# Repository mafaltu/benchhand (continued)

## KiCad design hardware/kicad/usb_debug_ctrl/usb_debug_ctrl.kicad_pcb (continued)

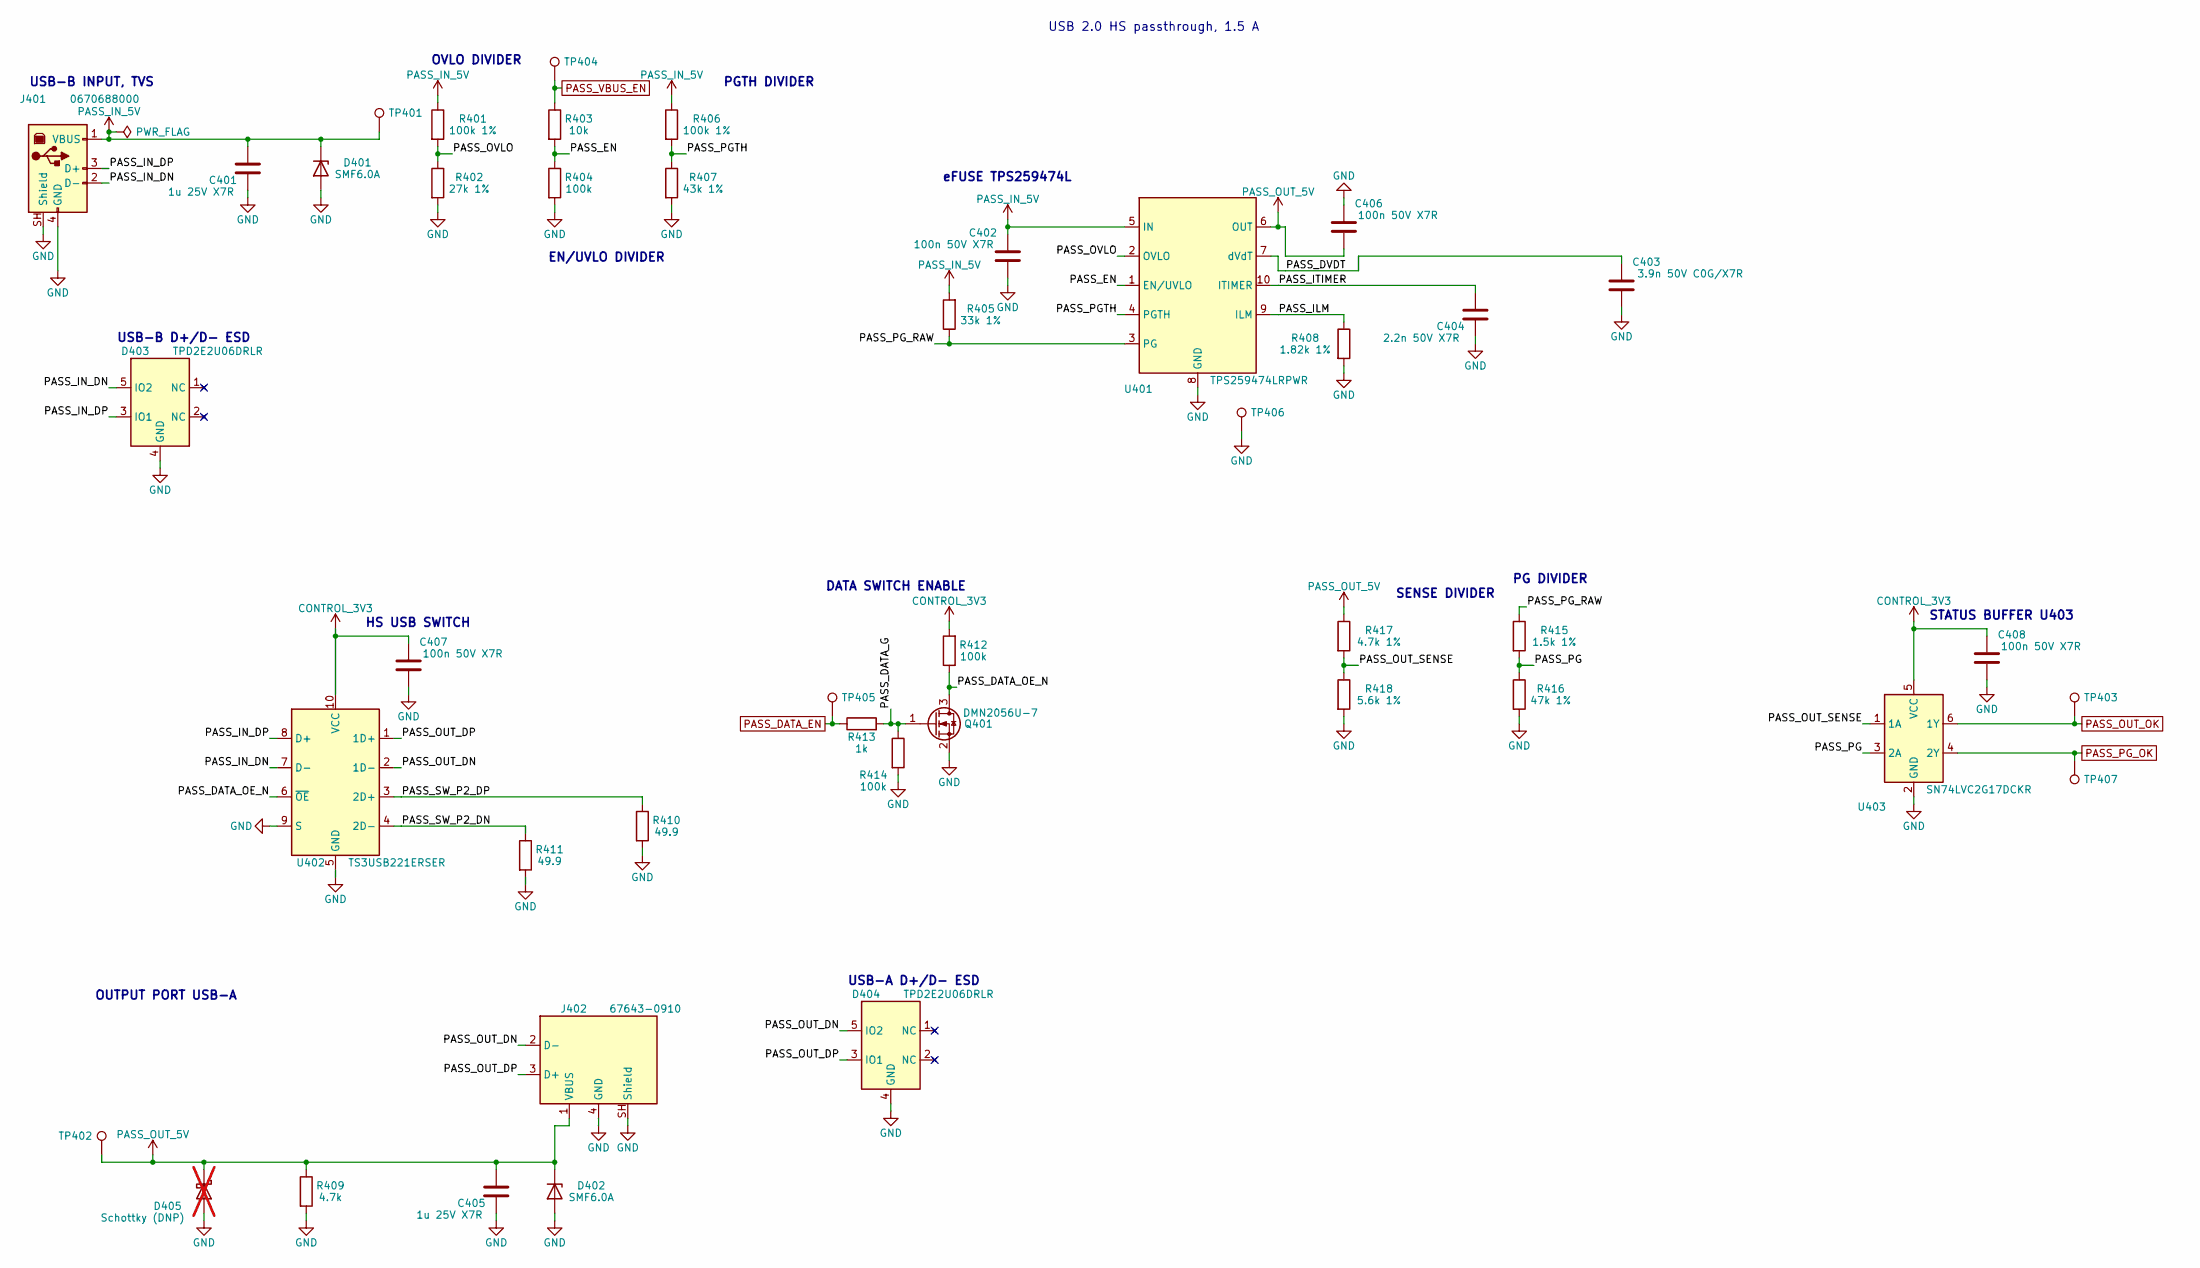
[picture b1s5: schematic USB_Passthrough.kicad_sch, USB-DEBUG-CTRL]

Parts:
C401, C405: 1u 25V X7R; C_0805_2012Metric; MPN CL21B105KAFNNNE
C402, C406, C407, C408: 100n 50V X7R; C_0603_1608Metric; MPN CC0603KRX7R9BB104
C403: 3.9n 50V C0G/X7R; C_0603_1608Metric; MPN CC0603KRX7R9BB392
C404: 2.2n 50V X7R; C_0603_1608Metric; MPN CL10B222KB8NNNC
D401, D402: SMF6.0A; D_SOD-123F_usb_relay; MPN SMF6.0A
D403, D404: TPD2E2U06DRLR; Texas_R-PDSO-N5_DRL-5_usb_relay; MPN TPD2E2U06DRLR
D405: Schottky (DNP); D_SOD-123; MPN none (DNP, MPN chosen only if the bench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; not fitted
J401: 0670688000; USB_B_Molex_67068-8000_Horizontal; MPN 0670688000
J402: 67643-0910; USB_A_Molex_67643_Horizontal; MPN 67643-0910
Q401: DMN2056U-7; SOT-23; MPN DMN2056U-7
R401, R406: 100k 1%; R_0603_1608Metric; MPN RC0603FR-07100KL
R402: 27k 1%; R_0603_1608Metric; MPN RC0603FR-0727KL
R403: 10k; R_0603_1608Metric; MPN RC0603FR-0710KL
R404, R412, R414: 100k; R_0603_1608Metric; MPN RC0603FR-07100KL
R405: 33k 1%; R_0603_1608Metric; MPN RC0603FR-0733KL
R407: 43k 1%; R_0603_1608Metric; MPN RC0603FR-0743KL
R408: 1.82k 1%; R_0603_1608Metric; MPN RC0603FR-071K82L
R409: 4.7k; R_0603_1608Metric; MPN RC0603FR-074K7L
R410, R411: 49.9; R_0603_1608Metric; MPN RC0603FR-0749R9L
R413: 1k; R_0603_1608Metric; MPN RC0603FR-071KL
R415: 1.5k 1%; R_0603_1608Metric; MPN RC0603FR-071K5L
R416: 47k 1%; R_0603_1608Metric; MPN RC0603FR-0747KL
R417: 4.7k 1%; R_0603_1608Metric; MPN RC0603FR-074K7L
R418: 5.6k 1%; R_0603_1608Metric; MPN RC0603FR-075K6L
TP401, TP402, TP403, TP404, TP405, TP406, TP407: test pad 1.0 mm; TestPoint_Pad_D1.0mm; MPN none (copper only)
U401: TPS259474LRPWR; Texas_RPW0010A_VQFN-HR-10_2x2mm; MPN TPS259474LRPWR
U402: TS3USB221ERSER; Texas_UQFN-10_1.5x2mm_P0.5mm_usb_relay; MPN TS3USB221ERSER
U403: SN74LVC2G17DCKR; SOT-363_SC-70-6; MPN SN74LVC2G17DCKR

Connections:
/USB_Passthrough/PASS_DATA_G: Q401.1 (G), R413.2, R414.1
/USB_Passthrough/PASS_DATA_OE_N: Q401.3 (D), R412.1, U402.6 (~OE)
/USB_Passthrough/PASS_DVDT: C403.1, U401.7 (dVdT)
/USB_Passthrough/PASS_EN: R403.2, R404.1, U401.1 (EN/UVLO)
/USB_Passthrough/PASS_ILM: R408.1, U401.9 (ILM)
/USB_Passthrough/PASS_IN_DN: D403.5 (IO2), J401.2 (D-), U402.7 (D-)
/USB_Passthrough/PASS_IN_DP: D403.3 (IO1), J401.3 (D+), U402.8 (D+)
/USB_Passthrough/PASS_ITIMER: C404.1, U401.10 (ITIMER)
/USB_Passthrough/PASS_OUT_DN: D404.5 (IO2), J402.2 (D-), U402.2 (1D-)
/USB_Passthrough/PASS_OUT_DP: D404.3 (IO1), J402.3 (D+), U402.1 (1D+)
/USB_Passthrough/PASS_OUT_SENSE: R417.2, R418.1, U403.1 (1A)
/USB_Passthrough/PASS_OVLO: R401.2, R402.1, U401.2 (OVLO)
/USB_Passthrough/PASS_PG: R415.2, R416.1, U403.3 (2A)
/USB_Passthrough/PASS_PGTH: R406.2, R407.1, U401.4 (PGTH)
/USB_Passthrough/PASS_PG_RAW: R405.1, R415.1, U401.3 (PG)
/USB_Passthrough/PASS_SW_P2_DN: R411.1, U402.4 (2D-)
/USB_Passthrough/PASS_SW_P2_DP: R410.1, U402.3 (2D+)
CONTROL_3V3: C407.1, C408.1, R412.2, U402.10 (VCC), U403.5 (VCC); also elsewhere on the board
GND: C401.2, C402.2, C403.2, C404.2, C405.2, C406.2, C407.2, C408.2, D401.2 (A), D402.2 (A), D403.4 (GND), D404.4 (GND), D405.2 (A), J401.4 (GND), J401.SH (Shield), J402.4 (GND), J402.SH (Shield), Q401.2 (S), R402.2, R404.2, R407.2, R408.2, R409.2, R410.2, R411.2, R414.2, R416.2, R418.2, TP406.1, U401.8 (GND), U402.5 (GND), U402.9 (S), U403.2 (GND); also elsewhere on the board
PASS_DATA_EN: R413.1, TP405.1; also elsewhere on the board
PASS_IN_5V: C401.1, C402.1, D401.1 (K), J401.1 (VBUS), R401.1, R405.2, R406.1, TP401.1, U401.5 (IN)
PASS_OUT_5V: C405.1, C406.1, D402.1 (K), D405.1 (K), J402.1 (VBUS), R409.1, R417.1, TP402.1, U401.6 (OUT)
PASS_OUT_OK: TP403.1, U403.6 (1Y); also elsewhere on the board
PASS_PG_OK: TP407.1, U403.4 (2Y); also elsewhere on the board
PASS_VBUS_EN: R403.1, TP404.1; also elsewhere on the board

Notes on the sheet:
USB-B INPUT, TVS
USB-B D+/D- ESD
OVLO DIVIDER
EN/UVLO DIVIDER
PGTH DIVIDER
eFUSE TPS259474L
HS USB SWITCH
DATA SWITCH ENABLE
SENSE DIVIDER
PG DIVIDER
STATUS BUFFER U403
OUTPUT PORT USB-A
USB-A D+/D- ESD
USB 2.0 HS passthrough, 1.5 A

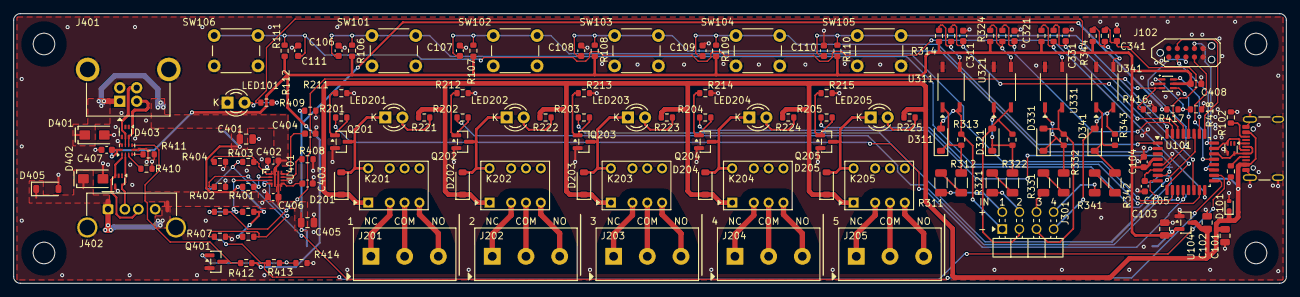
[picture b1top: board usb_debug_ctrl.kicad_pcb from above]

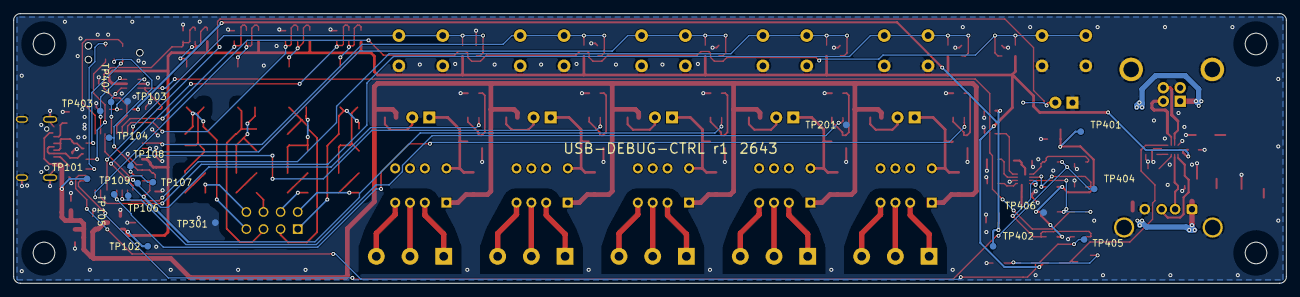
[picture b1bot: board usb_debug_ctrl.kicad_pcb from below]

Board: 2 copper layers, 188.8 x 40.0 mm, 165 parts (18 on the bottom side), 102 nets.

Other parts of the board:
MH1, MH2, MH3, MH4: MountingHole_M3_NPTH_3.2mm_keepout7

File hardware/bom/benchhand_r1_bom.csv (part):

Refs,Qty,Value,Description,Key spec,Package,Manufacturer,MPN,Substitution,Fitting,Mouser,DigiKey,TME,LCSC,Notes
U101,1,STM32C071K8T6,"MCU Arm Cortex-M0+, native crystal-less USB FS","STM32C071K8T6, LQFP-32 7x7 mm 0.8 mm pitch",LQFP-32 7x7 mm,STMicroelectronics,STM32C071K8T6,no substitute without footprint/datasheet check: firmware and pin map are built for this exact MCU,SMD top,511-STM32C071K8T6,497-STM32C071K8T6-ND,,,
U104,1,3.3 V LDO,3.3 V LDO regulator for CONTROL_3V3,"3.3 V fixed LDO, >= 250 mA, input rating >= 16 V, SOT-23-3 pinout as MCP1703A SOT-23A",SOT-23-3 (SOT-23A),Microchip,MCP1703AT-3302E/CB,no substitute without footprint/datasheet check: SOT-23 LDO pinouts differ between vendors; must be stable with the 4.7 uF X7R output capacitor C103,SMD top,579-MCP1703AT3302ECB,MCP1703AT-3302E/CBCT-ND,,C144183,
U401,1,TPS259474L,"eFuse, true reverse blocking, latch-off, power-good output (passthrough VBUS)","TPS259474L variant (adjustable OVLO + PG, latch-off), VQFN-HR-10 2x2 mm (RPW)",VQFN-HR-10 2x2 mm (RPW),Texas Instruments,TPS259474LRPWR,"no substitute without footprint/datasheet check: variant fixed by D-23; TPS259474A (auto-retry) and other TPS25947x variants differ in fault response / pin function; ILIM, OVLO and PGTH resistors are sized for this part",SMD top,595-TPS259474LRPWR,296-TPS259474LRPWRCT-ND,,C2864845,"Current limit set by R408 1.82k for the 1.5 A USB receptacles (D-36, D-39)."
U402,1,TS3USB221E,"USB 2.0 high-speed 1:2 analog switch, used as passthrough data on/off","TS3USB221E, VCC 2.3-3.6 V, 1 GHz bandwidth, UQFN-10 2x1.5 mm 0.5 mm pitch (RSE)",UQFN-10 2x1.5 mm (RSE),Texas Instruments,TS3USB221ERSER,"no substitute without footprint/datasheet check: USB 2.0 HS data path, TI RSE0010A land pattern",SMD top,595-TS3USB221ERSER,296-25222-1-ND,,,"Fine pitch: stencil area ratio 0.61, inspect the paste print and joints (assembly notes section 2)."
U403,1,SN74LVC2G17,"dual Schmitt-trigger buffer, passthrough status to MCU","non-inverting dual Schmitt buffer, 5.5 V tolerant inputs, Ioff partial power-down, SC70-6 (DCK)",SC70-6 (SOT-363),Texas Instruments,SN74LVC2G17DCKR,"no substitute without footprint/datasheet check: inputs see 5 V-domain dividers, also with VCC off (D-44); SN74LVC2G14 is inverting (firmware change)",SMD top,595-SN74LVC2G17DCKR,296-13013-1-ND,,,
U311 U321 U331 U341,4,ISOM8600,"opto-emulator switch 80 V 150 mA, functionally isolated inputs IN1-IN4","ISOM8600DFGR, 4-pin SOIC (DFG)",SO-4 4.4x3.6 mm 2.54 mm pitch (DFG),Texas Instruments,ISOM8600DFGR,no substitute without footprint/datasheet check: input network R3x1/R3x2/R3x3 sized for the ISOM8600 diode-emulator input (D-25); custom footprint,SMD top,595-ISOM8600DFGR,296-ISOM8600DFGRCT-ND,,,
D403 D404 U102,3,TPD2E2U06,dual-channel ESD array for USB D+/D-,"2-channel ESD, VRWM 5.5 V, IO capacitance 1.5 pF typ, 5-pin SOT (DRL)","SOT-553 (DRL, 5-pin)",Texas Instruments,TPD2E2U06DRLR,"no substitute without footprint/datasheet check: low-capacitance USB 2.0 HS ESD, DRL pinout",SMD top,595-TPD2E2U06DRLR,296-38361-1-ND,,,"U102 at J101, D403 at J401, D404 at J402."
D101,1,TPD1E10B06,bidirectional ESD clamp on CONTROL_5V,"1-channel bidirectional ESD TVS, VRWM 5.5 V, SOD-523",SOD-523 (DYA),Texas Instruments,TPD1E10B06DYAR,"no substitute without footprint/datasheet check: bidirectional, VRWM 5.5 V, SOD-523 land pattern (D-39)",SMD top,595-TPD1E10B06DYAR,296-TPD1E10B06DYARCT-ND,,,
Q201 Q202 Q203 Q204 Q205 Q401,6,DMN2056U,"N-channel MOSFET: relay coil drivers Q201-Q205, /OE inverter Q401","N-MOSFET 20 V, RDS(on) <= 45 mOhm @ VGS 2.5 V, VGS(th) <= 1.0 V, SOT-23 G=1 S=2 D=3",SOT-23,Diodes Incorporated,DMN2056U-7,"no substitute without footprint/datasheet check: logic-level gate driven from 3.3 V, SOT-23 pinout G=1 S=2 D=3 (D-40)",SMD top,621-DMN2056U-7,DMN2056U-7DICT-ND,DMN2056U-7,C332302,
D201 D202 D203 D204 D205 D311 D321 D331 D341,9,1N4148W,"switching diode: relay flyback D201-D205, input reverse clamps D311-D341","1N4148W small-signal diode, IR < 25 nA @ 20 V 25 C, VF < 1 V @ 50 mA, SOD-123F or SOD-123",SOD-123F (fits SOD-123 pads),Diotec Semiconductor,1N4148W,"any part meeting key spec (low reverse leakage matters for D311-D341, D-59)",SMD top,,,1N4148W-DIO,,
D401 D402,2,SMF6.0A,unidirectional TVS on PASS_IN_5V,"unidirectional TVS, VRWM 6.0 V, VBR 6.6-7.4 V @ 10 mA, VC 10.3 V, SOD-123FL",SOD-123FL,Diotec Semiconductor,SMF6.0A,"any part meeting key spec (SOD-123FL, cathode marked)",SMD top,637-SMF6.0A,,SMF6.0A-DIO,,"Mouser code 637-SMF6.0A from design/bom_lock.csv note (same Diotec part, D-59)."
J101,1,USB-C 2.0,"USB-C 2.0 receptacle, control port","USB-C 2.0 receptacle 16-pin, top mount horizontal, SMT signal pins + THT shell legs",GCT USB4105 land pattern,GCT,USB4105-GF-A,no substitute without footprint/datasheet check: GCT USB4105 land pattern (D-79),SMD top + hand-solder (shell legs),640-USB4105-GF-A,2073-USB4105-GF-ACT-ND,USB4105-GF-A,C3020560,Inspect the solder mask over the VBUS bridge under the shell before placing (assembly notes section 3).
J401,1,USB-B 2.0,"USB-B 2.0 receptacle, THT right angle, passthrough input","full-size USB-B 2.0 receptacle, THT right angle, >= 1.5 A","THT, Molex 67068-8000 drawing",Molex,0670688000,no substitute without footprint/datasheet check: custom Molex 67068-8000 footprint; passthrough rating 1.5 A follows this connector (D-36),THT (hand-solder after reflow),538-67068-8000,,MX-67068-8000,,Molex 67068-8000 = 0670688000. Mouser code from the project lock (Mouser shows no exact MPN match); TME code MX-67068-8000 from design/bom_lock.csv note (D-40).
J402,1,USB-A 2.0,"USB-A 2.0 receptacle, THT right angle, passthrough output to DUT","USB-A 2.0 receptacle, THT right angle, Molex 67643 footprint","THT, Molex 67643",Molex,67643-0910,no substitute without footprint/datasheet check: KiCad Molex 67643 footprint (D-49),THT (hand-solder after reflow),538-67643-0910,WM4993-ND,MX-67643-0910,,-0910 is for hand soldering only (no IR reflow).
J201 J202 J203 J204 J205,5,3-pos 5.0 mm,"PCB screw terminal, relay contacts NC/COM/NO","3-position PCB screw terminal, 5.0 mm pitch, 1.30 mm holes, wire entry toward the board edge, 15 A / 300 V (D-40)",THT 3-pos 5.0 mm,Same Sky,TB002-500-03BE,"no substitute without footprint/datasheet check: hole size, pitch and wire-entry direction",THT (hand-solder after reflow),490-TB002-500-03BE,,,,
J301,1,2x4 RA header,"2x4 right-angle male header 2.54 mm, isolated inputs IN1-IN4","2x4 male header 2.54 mm, right angle, Samtec lead style -08",THT 2x4 2.54 mm right angle,Samtec,TSW-104-08-F-D-RA,"alternate: Samtec TSW-104-08-T-D-RA (matte tin, same footprint, D-60); any other header needs a pin-1 / row check (D-48)",THT (hand-solder after reflow),200-TSW10408FDRA,,,,
K201 K202 K203 K204 K205,5,HFD4/5,"signal relay 5 V coil DPDT, channels 1-5","Hongfa HFD4/5: 5 V coil, DPDT, THT","THT, custom HFD4 footprint",Hongfa,HFD4/5,no substitute without footprint/datasheet check: custom HFD4 footprint; coil drive and pick-up margin analysed for HFD4 (D-29),THT (hand-solder after reflow),,,HFD4/5,,"HFD4/4.5 (4.5 V coil, more pick-up margin) is preferred if purchasable (D-29); with HFD4/5 keep VBUS >= 4.6 V at the board."
SW101 SW102 SW103 SW104 SW105 SW106,6,tact 6x6,"tactile switch, relay and USB buttons","tact switch 6x6 mm THT, actuator 13.0 mm above PCB, 160 gf","THT 6x6 mm, hole pattern 6.5x4.5 mm",Same Sky,TS02-66-130-BK-160-LCR-D,no substitute without footprint/datasheet check: actuator height must match the enclosure; hole pattern 6.5 x 4.5 mm,THT (hand-solder after reflow),179-TS0266130BK160LC,,TS0266130BK160LCRD,,
LED101 LED201 LED202 LED203 LED204 LED205,6,green 3 mm,"LED: LED101 USB state, LED201-LED205 relay coil state","3 mm green diffused THT LED, VF typ 1.9 V / max 2.2 V @ 2 mA",THT 3 mm,Kingbright,L-934LGD,"any part meeting key spec (3 mm THT, ~2 mA drive; series resistors R112 / R221-R225 sized for this LED, D-58)",THT (hand-solder after reflow),,,L-934LGD,,
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
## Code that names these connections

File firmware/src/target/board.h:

/* SPDX-License-Identifier: GPL-3.0-or-later
 * Copyright (c) 2026 Martin Faltus (mafaltu) */
#ifndef TARGET_BOARD_H
#define TARGET_BOARD_H
#include <stdbool.h>

#include "core/app.h"

/* Board pin layer, USB-DEBUG-CTRL r1 (spec 2, onboarding pin map; design/pinmap_checks.md):
 *   RLY1..5      PA5, PA4, PA1, PA0, PB3   output, high = coil ON (100 k gate pull-down)
 *   LED_USB      PA7                       output, high = on
 *   PASS_VBUS_EN PB2, PASS_DATA_EN PA8     output, high = ON (hardware default OFF)
 *   BTN_RLY1..5  PB0, PA3, PC14, PB9, PB8  input, active low (100 k pull-up, RC)
 *   BTN_USB      PB1                       input, active low
 *   IN1..4       PA2, PB7, PB6, PB5        input, GPIO low = isolated input HIGH (22 k pull-up)
 *   PASS_PG_OK   PB4, PASS_OUT_OK PA15     input, high = OK (push-pull buffer U403), polled
 *   unused       PA6, PA9, PA10, PC15, PC6 analog; PA11/PA12 analog until USB takes them (Task 10)
 *   SWD          PA13, PA14                left in their reset (AF) state */

/* Spec 4.4: output data registers are written 0 before any pin becomes an output. Call first in main(). */
void board_init_safe(void);

/* Samples all inputs once and applies the active-low inversions. */
void board_read(app_in_t *in);

/* The single place that drives the output pins (one BSRR write per port). */
void board_write(const app_out_t *out);

/* 96-bit UID (UID_BASE words 0, 1, 2, each most significant nibble first) as 24 upper-case hex chars + NUL. */
void board_uid_hex(char out[25]);

#endif
